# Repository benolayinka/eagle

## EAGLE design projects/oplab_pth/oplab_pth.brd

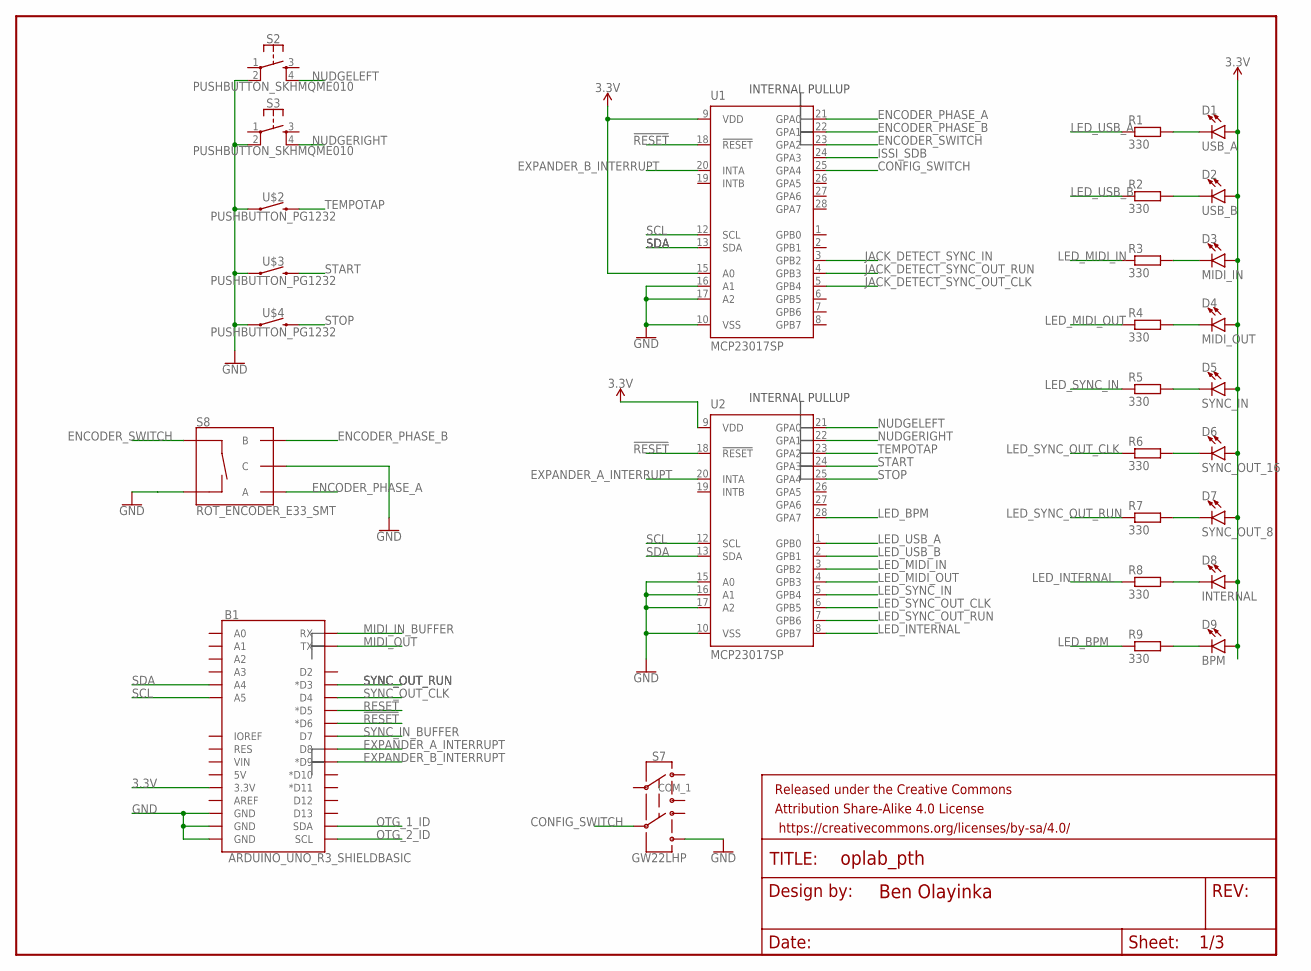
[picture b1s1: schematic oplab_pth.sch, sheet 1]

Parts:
B1: ARDUINO_UNO_R3_SHIELDBASIC; UNO_R3_SHIELD
D1: USB_A; LED_5MM
D2: USB_B; LED_5MM
D3: MIDI_IN; LED_5MM
D4: MIDI_OUT; LED_5MM
D5: SYNC_IN; LED_5MM
D6: SYNC_OUT_16; LED_5MM
D7: SYNC_OUT_8; LED_5MM
D8: INTERNAL; LED_5MM
D9: BPM; LED_5MM
FRAME1: FRAME-LETTERNO_PACKAGE; DUMMY
R1, R2, R3, R4, R5, R6, R7, R8, R9: 330; 0207/10
S2, S3: PUSHBUTTON_SKHMQME010; PUSHUTTON_SKHMQLE010
S7: GW22LHP
S8: ROT_ENCODER_E33_SMT
U1, U2: MCP23017SP; DIL28-3
U$2, U$3, U$4: PUSHBUTTON_PG1232

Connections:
3.3V: B1.3.3V, D1.A, D2.A, D3.A, D4.A, D5.A, D6.A, D7.A, D8.A, D9.A, U1.9 (VDD), U1.15 (A0), U2.9 (VDD); also elsewhere on the board
!RESET: B1.D6 (*D6), U1.18 (!RESET), U2.18 (!RESET)
CONFIG_SWITCH: S7.5 (COM_2), U1.25 (GPA4)
ENCODER_PHASE_A: S8.A, U1.21 (GPA0)
ENCODER_PHASE_B: S8.B, U1.22 (GPA1)
ENCODER_SWITCH: S8.S1 (SW+), U1.23 (GPA2)
EXPANDER_A_INTERRUPT: B1.D8, U2.20 (INTA)
EXPANDER_B_INTERRUPT: B1.D9 (*D9), U1.20 (INTA)
GND: B1.GND@0 (GND), B1.GND@1 (GND), B1.GND@2 (GND), S2.2, S3.2, S7.4 (NO_2), S8.C, S8.S2 (SW-), U1.10 (VSS), U1.16 (A1), U1.17 (A2), U2.10 (VSS), U2.15 (A0), U2.16 (A1), U2.17 (A2), U$2.1, U$3.1, U$4.1; also elsewhere on the board
ISSI_SDB: U1.24 (GPA3); also elsewhere on the board
JACK_DETECT_SYNC_IN: U1.3 (GPB2); also elsewhere on the board
JACK_DETECT_SYNC_OUT_CLK: U1.5 (GPB4); also elsewhere on the board
JACK_DETECT_SYNC_OUT_RUN: U1.4 (GPB3); also elsewhere on the board
LED_BPM: R9.1, U2.28 (GPA7)
LED_INTERNAL: R8.1, U2.8 (GPB7)
LED_MIDI_IN: R3.1, U2.3 (GPB2)
LED_MIDI_OUT: R4.1, U2.4 (GPB3)
LED_SYNC_IN: R5.1, U2.5 (GPB4)
LED_SYNC_OUT_CLK: R6.1, U2.6 (GPB5)
LED_SYNC_OUT_RUN: R7.1, U2.7 (GPB6)
LED_USB_A: R1.1, U2.1 (GPB0)
LED_USB_B: R2.1, U2.2 (GPB1)
MIDI_IN_BUFFER: B1.RX; also elsewhere on the board
MIDI_OUT: B1.TX; also elsewhere on the board
unnamed: D1.K (C), R1.2
unnamed: D2.K (C), R2.2
unnamed: D3.K (C), R3.2
unnamed: D4.K (C), R4.2
unnamed: D5.K (C), R5.2
unnamed: D6.K (C), R6.2
unnamed: D7.K (C), R7.2
unnamed: D8.K (C), R8.2
unnamed: D9.K (C), R9.2
NUDGELEFT: S2.4, U2.21 (GPA0)
NUDGERIGHT: S3.4, U2.22 (GPA1)
OTG_1_ID: B1.SDA
OTG_2_ID: B1.SCL
RESET: B1.D5 (*D5); also elsewhere on the board
SCL: B1.A5, U1.12 (SCL), U2.12 (SCL); also elsewhere on the board
SDA: B1.A4, U1.13 (SDA), U2.13 (SDA); also elsewhere on the board
START: U2.24 (GPA3), U$3.2
STOP: U2.25 (GPA4), U$4.2
SYNC_IN_BUFFER: B1.D7; also elsewhere on the board
SYNC_OUT_CLK: B1.D4; also elsewhere on the board
SYNC_OUT_RUN: B1.D3 (*D3); also elsewhere on the board
TEMPOTAP: U2.23 (GPA2), U$2.2

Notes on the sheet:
INTERNAL PULLUP

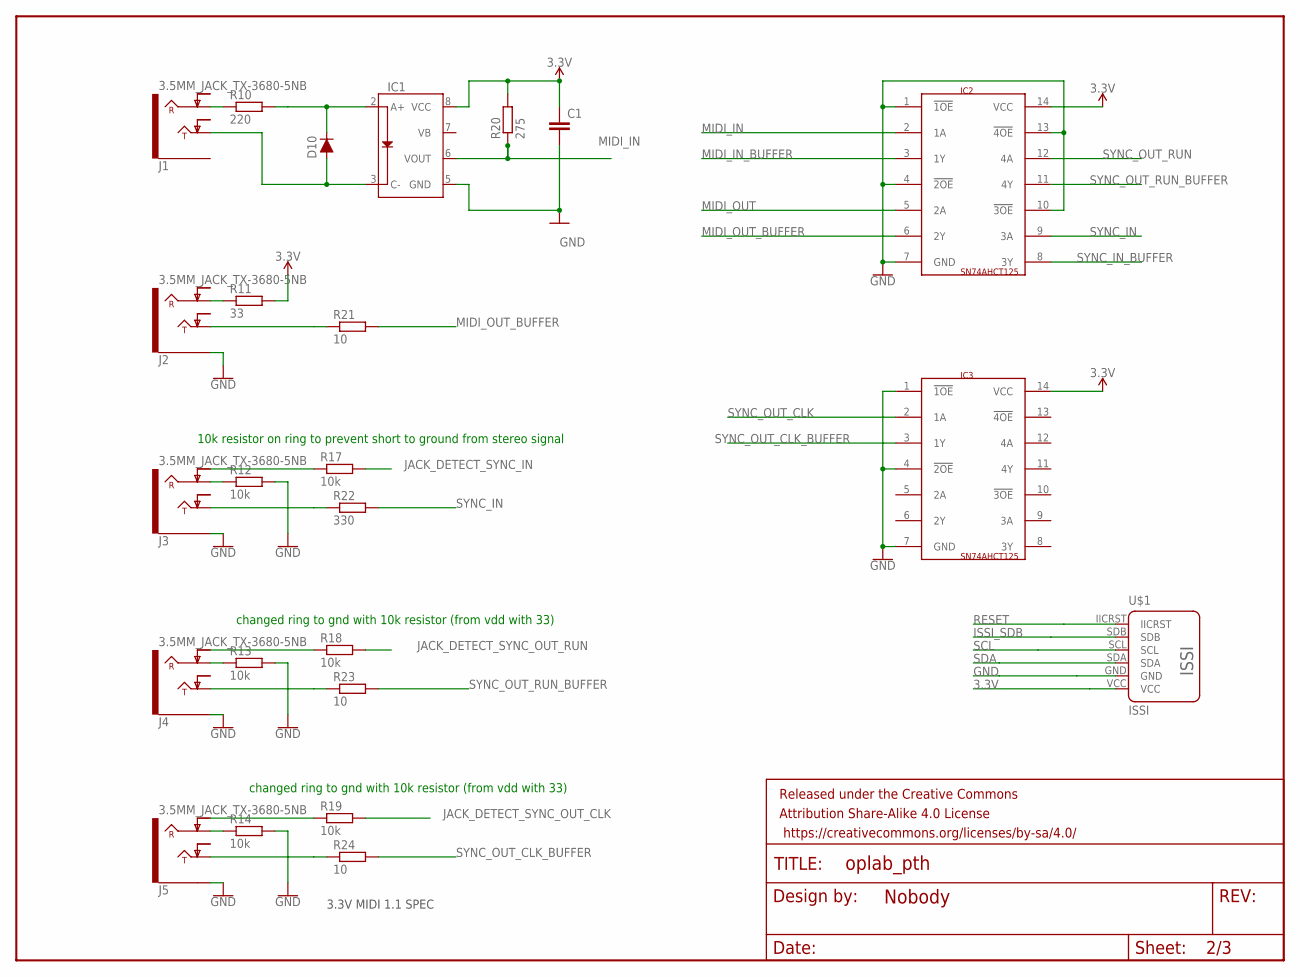
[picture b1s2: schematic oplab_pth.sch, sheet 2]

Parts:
C1: C-EU025-024X044; C025-024X044
D10: 200mA/100V/1V; DIODE-1N4148
FRAME2: FRAME-LETTERNO_PACKAGE; DUMMY
IC1: OPTO_DARLINGTON_HCPL0701; OPTO_DARLINGTON_SOIC127P594X363-8N
IC2, IC3: SN74AHCT125; SN74AHCT_DIP794W53P254L1930H508Q14N
J1, J2, J3, J4, J5: 3.5MM_JACK_TX-3680-5NB; 3.5MM_JACK_TX36805NB
R10: 220; 0207/10
R11: 33; 0207/10
R12, R13, R14, R17, R18, R19: 10k; 0207/10
R20: 275; 0207/10
R21, R23, R24: 10; 0207/10
R22: 330; 0207/10
U$1: ISSI

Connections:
3.3V: C1.1, IC1.8 (VCC), IC2.14 (VCC), IC3.14 (VCC), R11.2, R20.2, U$1.VCC; also elsewhere on the board
GND: C1.2, IC1.5 (GND), IC2.1 (!1OE), IC2.4 (!2OE), IC2.7 (GND), IC2.10 (!3OE), IC2.13 (!4OE), IC3.1 (!1OE), IC3.4 (!2OE), IC3.7 (GND), J2.1.EARTH (EARTH), J3.1.EARTH (EARTH), J4.1.EARTH (EARTH), J5.1.EARTH (EARTH), R12.2, R13.2, R14.2, U$1.GND; also elsewhere on the board
ISSI_SDB: U$1.SDB; also elsewhere on the board
JACK_DETECT_SYNC_IN: R17.2; also elsewhere on the board
JACK_DETECT_SYNC_OUT_CLK: R19.2; also elsewhere on the board
JACK_DETECT_SYNC_OUT_RUN: R18.2; also elsewhere on the board
MIDI_IN: IC1.6 (VOUT), IC2.2 (1A), R20.1
MIDI_IN_BUFFER: IC2.3 (1Y); also elsewhere on the board
MIDI_OUT: IC2.5 (2A); also elsewhere on the board
MIDI_OUT_BUFFER: IC2.6 (2Y), R21.2
unnamed: D10.C, IC1.2 (A+), R10.2
unnamed: D10.A, IC1.3 (C-), J1.2.TIP (TIP)
unnamed: J1.3.RING (RING), R10.1
unnamed: J2.3.RING (RING), R11.1
unnamed: J3.3.RING (RING), R12.1
unnamed: J4.3.RING (RING), R13.1
unnamed: J5.3.RING (RING), R14.1
unnamed: J2.2.TIP (TIP), R21.1
unnamed: J3.2.TIP (TIP), R22.1
unnamed: J4.2.TIP (TIP), R23.1
unnamed: J5.2.TIP (TIP), R24.1
unnamed: J3.5.RINGNORM (RING-NORM), R17.1
unnamed: J4.5.RINGNORM (RING-NORM), R18.1
unnamed: J5.5.RINGNORM (RING-NORM), R19.1
RESET: U$1.IICRST; also elsewhere on the board
SCL: U$1.SCL; also elsewhere on the board
SDA: U$1.SDA; also elsewhere on the board
SYNC_IN: IC2.9 (3A), R22.2
SYNC_IN_BUFFER: IC2.8 (3Y); also elsewhere on the board
SYNC_OUT_CLK: IC3.2 (1A); also elsewhere on the board
SYNC_OUT_CLK_BUFFER: IC3.3 (1Y), R24.2
SYNC_OUT_RUN: IC2.12 (4A); also elsewhere on the board
SYNC_OUT_RUN_BUFFER: IC2.11 (4Y), R23.2

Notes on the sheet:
3.3V MIDI 1.1 SPEC
10k resistor on ring to prevent short to ground from stereo signal
changed ring to gnd with 10k resistor (from vdd with 33)

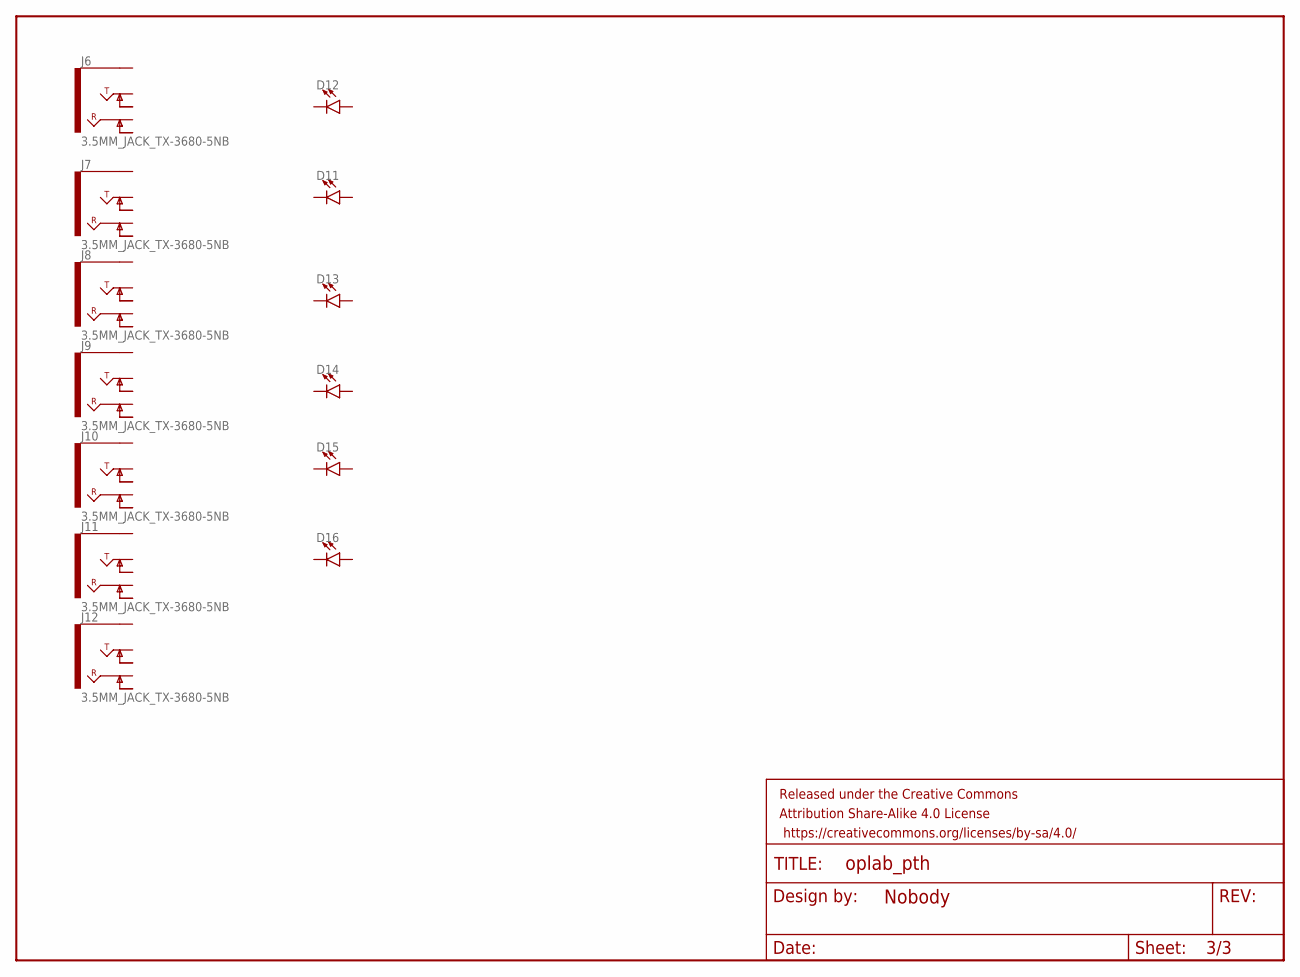
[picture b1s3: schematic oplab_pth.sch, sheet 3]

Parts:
D11, D12, D13, D14, D15, D16: LED5MM; LED_5MM
FRAME3: FRAME-LETTERNO_PACKAGE; DUMMY
J6, J7, J8, J9, J10, J11, J12: 3.5MM_JACK_TX-3680-5NB; 3.5MM_JACK_TX36805NB

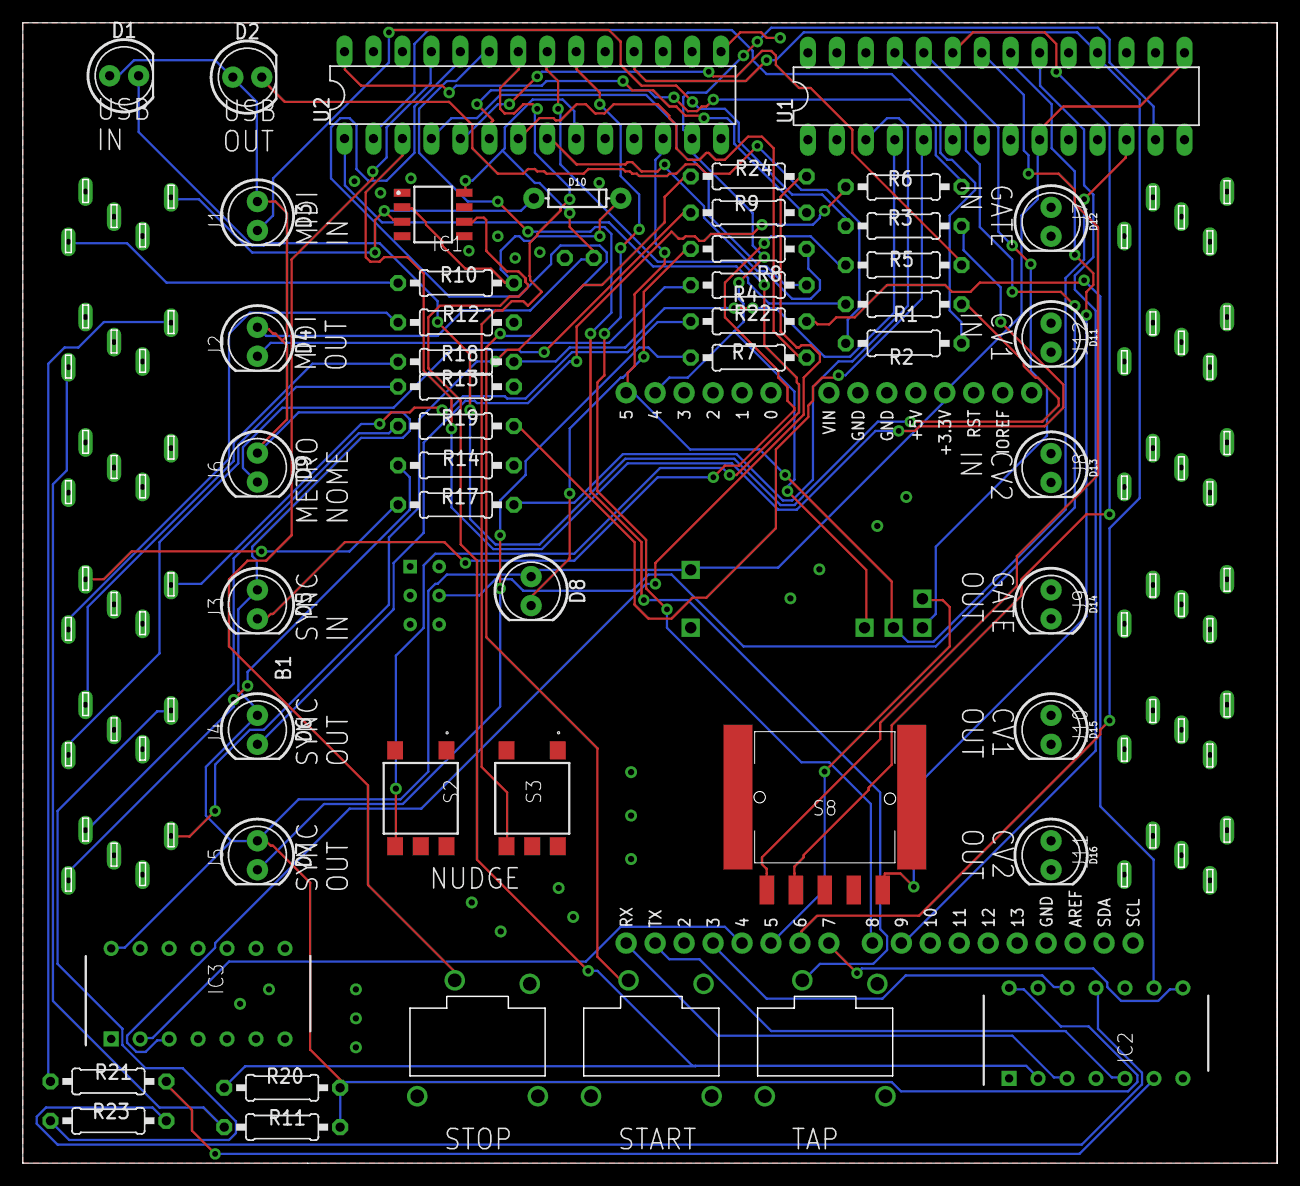
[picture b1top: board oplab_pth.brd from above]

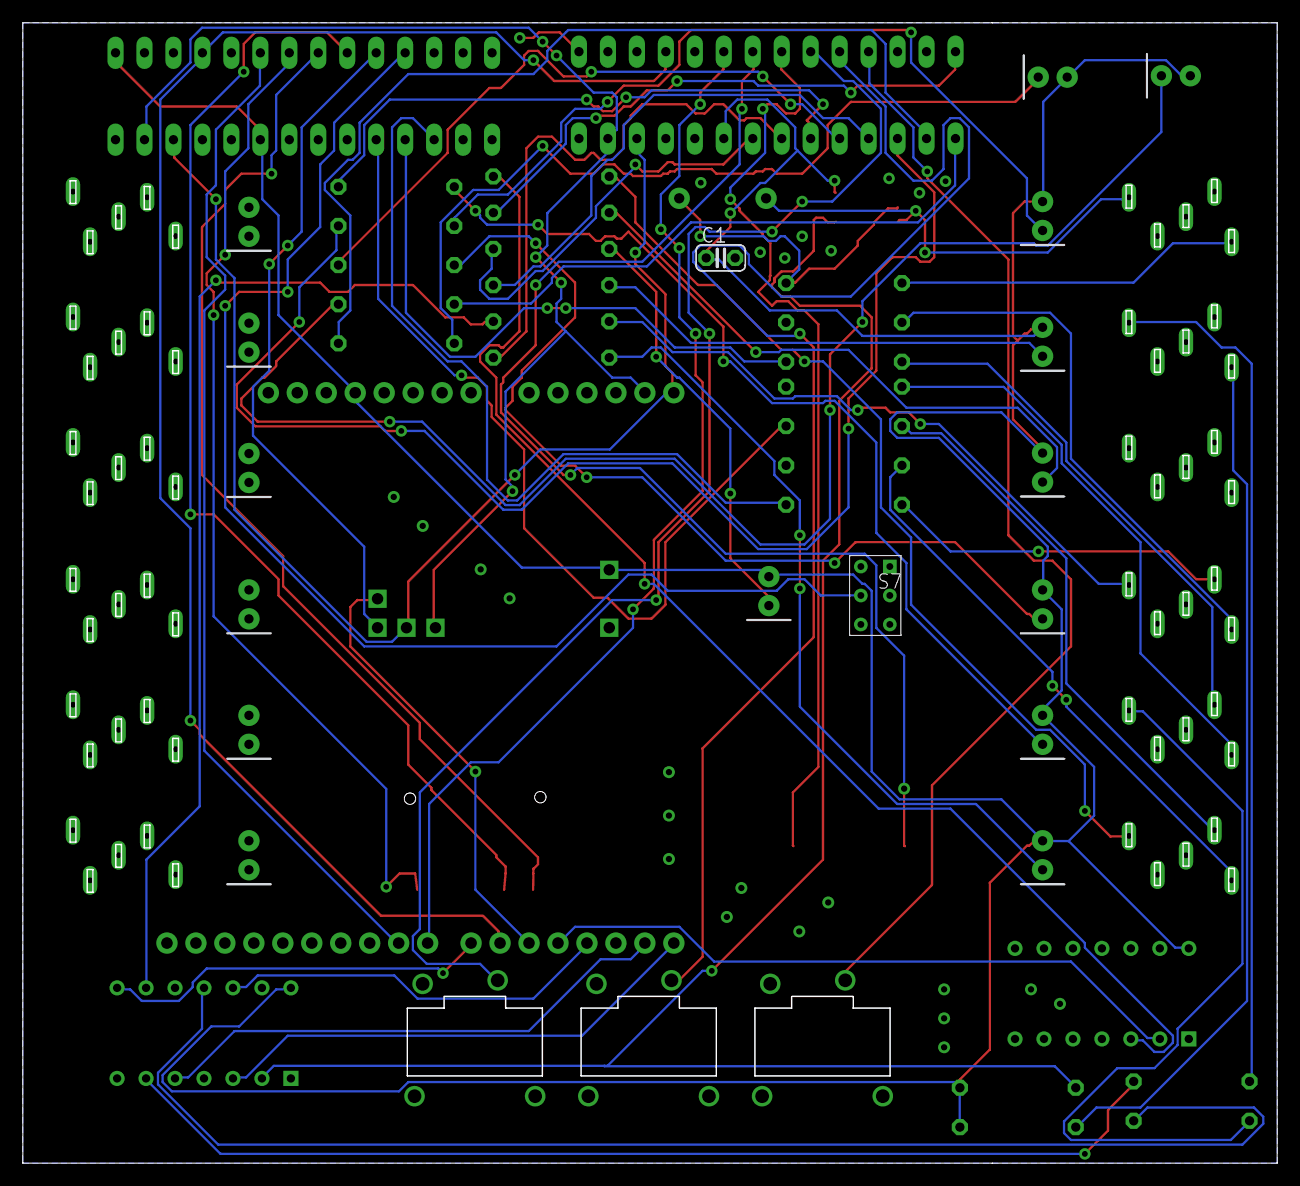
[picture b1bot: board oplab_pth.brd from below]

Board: 2 copper layers, 110.0 x 100.0 mm, 68 parts (2 on the bottom side), 63 nets.

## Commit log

2019-10-01 first
2019-10-01 lights

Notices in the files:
parts and their libraries:
SparkFun-Aesthetics: Licensing: Creative Commons ShareAlike 4.0 International - https://creativecommons.org/licenses/by-sa/4.0
SparkFun-Aesthetics: Released under the Creative Commons Attribution Share-Alike 4.0 License
SparkFun-Aesthetics: https://creativecommons.org/licenses/by-sa/4.0
